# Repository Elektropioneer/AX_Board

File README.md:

# AX_Board
Arduino Nano with support for AX-12A servos with additional buck dc/dc converter

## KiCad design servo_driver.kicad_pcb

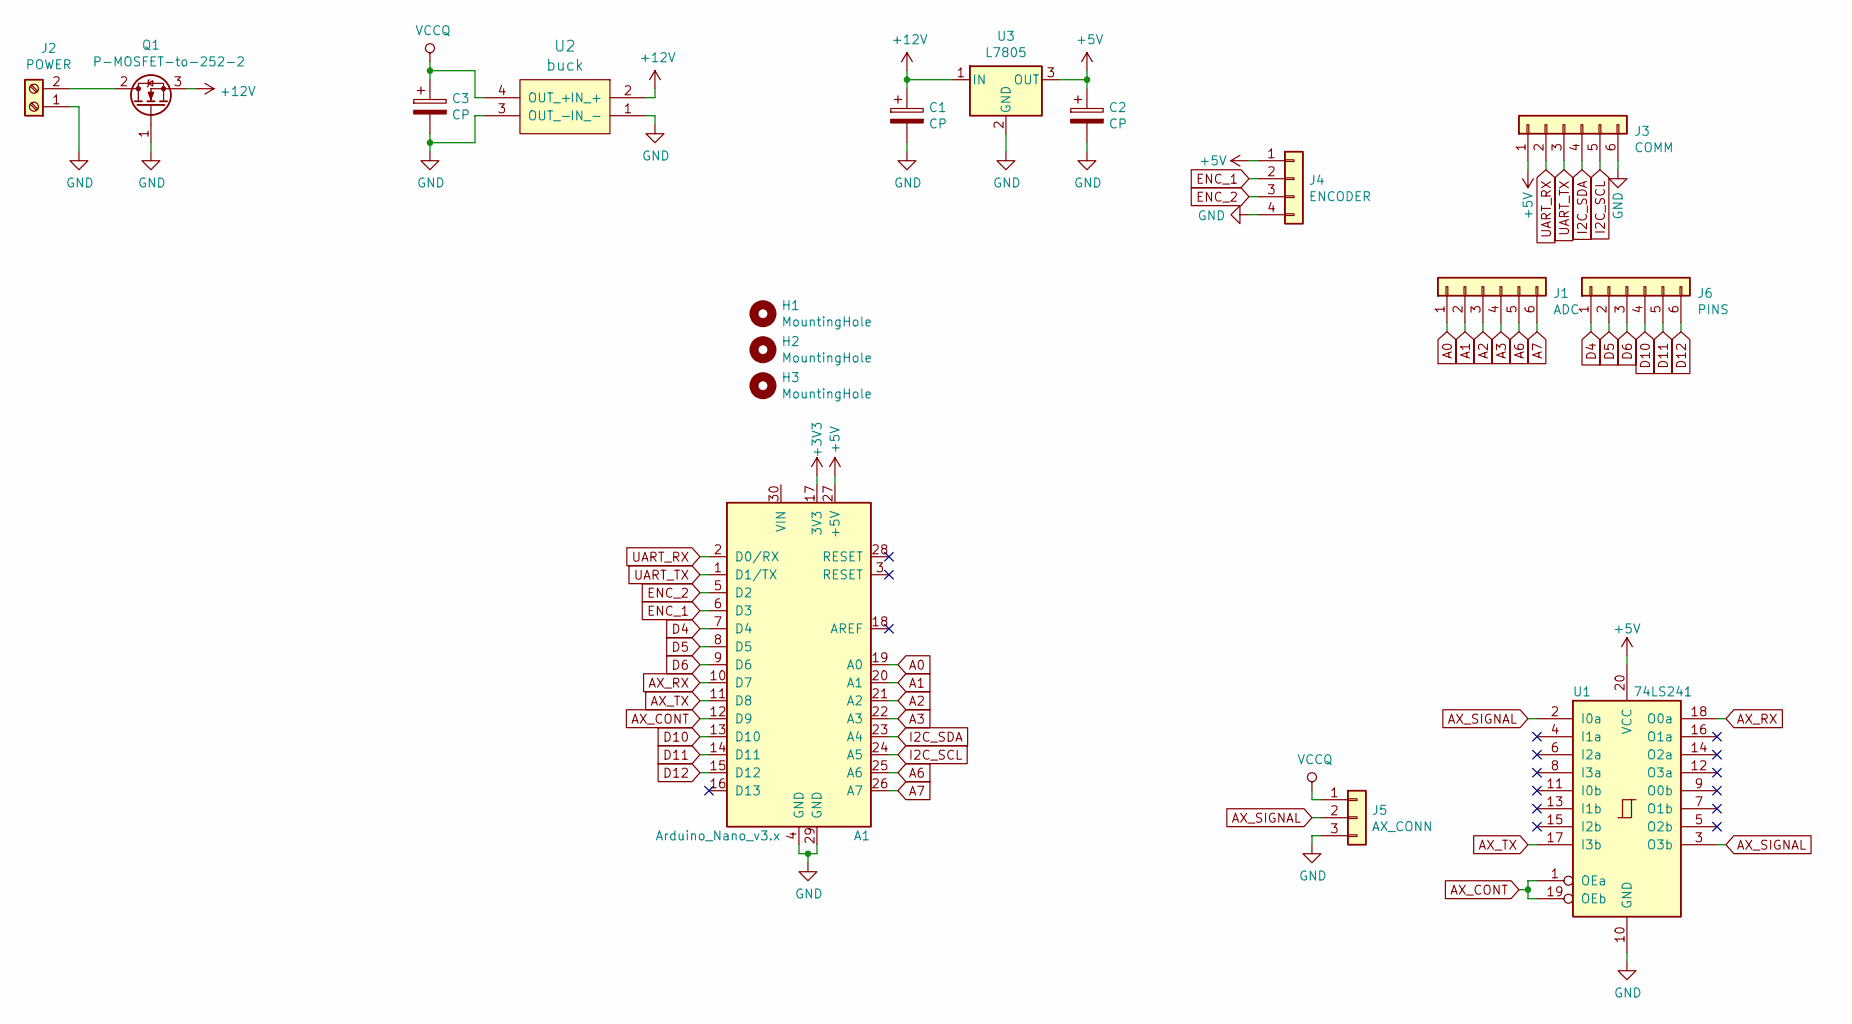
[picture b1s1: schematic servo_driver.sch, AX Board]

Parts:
A1: Arduino_Nano_v3.x; Arduino_Nano
C1, C2, C3: CP; CP_Elec_5x5.8
H1, H2, H3: MountingHole; MountingHole_3.2mm_M3_DIN965_Pad
J1: ADC; PinHeader_1x06_P2.54mm_Vertical
J2: POWER; TerminalBlock_Phoenix_MKDS-1,5-2_1x02_P5.00mm_Horizontal
J3: COMM; PinHeader_1x06_P2.54mm_Vertical
J4: ENCODER; PinHeader_1x04_P2.54mm_Vertical
J5: AX_CONN; TerminalBlock_Phoenix_MKDS-1,5-3_1x03_P5.00mm_Horizontal
J6: PINS; PinHeader_1x06_P2.54mm_Vertical
Q1: P-MOSFET-to-252-2; TO-252-2
U1: 74LS241; DIP-20_W7.62mm
U2: buck
U3: L7805; TO-252-2

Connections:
+3V3: A1.17 (3V3)
+5V: A1.27 (+5V), C2.1, J3.1, J4.1, U1.20 (VCC), U3.3 (OUT)
+12V: C1.1, Q1.3 (S), U2.2 (IN_+), U3.1 (IN)
A0: A1.19 (A0), J1.1
A1: A1.20 (A1), J1.2
A2: A1.21 (A2), J1.3
A3: A1.22 (A3), J1.4
A6: A1.25 (A6), J1.5
A7: A1.26 (A7), J1.6
AX_CONT: A1.12 (D9), U1.1 (OEa), U1.19 (OEb)
AX_RX: A1.10 (D7), U1.18 (O0a)
AX_SIGNAL: J5.2, U1.2 (I0a), U1.3 (O3b)
AX_TX: A1.11 (D8), U1.17 (I3b)
D4: A1.7 (D4), J6.1
D5: A1.8 (D5), J6.2
D6: A1.9 (D6), J6.3
D10: A1.13 (D10), J6.4
D11: A1.14 (D11), J6.5
D12: A1.15 (D12), J6.6
ENC_1: A1.6 (D3), J4.2
ENC_2: A1.5 (D2), J4.3
GND: A1.4 (GND), A1.29 (GND), C1.2, C2.2, C3.2, J2.1, J3.6, J4.4, J5.3, Q1.1 (G), U1.10 (GND), U2.1 (IN_-), U2.3 (OUT_-), U3.2 (GND)
I2C_SCL: A1.24 (A5), J3.5
I2C_SDA: A1.23 (A4), J3.4
unnamed: J2.2, Q1.2 (D)
UART_RX: A1.2 (D0/RX), J3.2
UART_TX: A1.1 (D1/TX), J3.3
VCCQ: C3.1, J5.1, U2.4 (OUT_+)

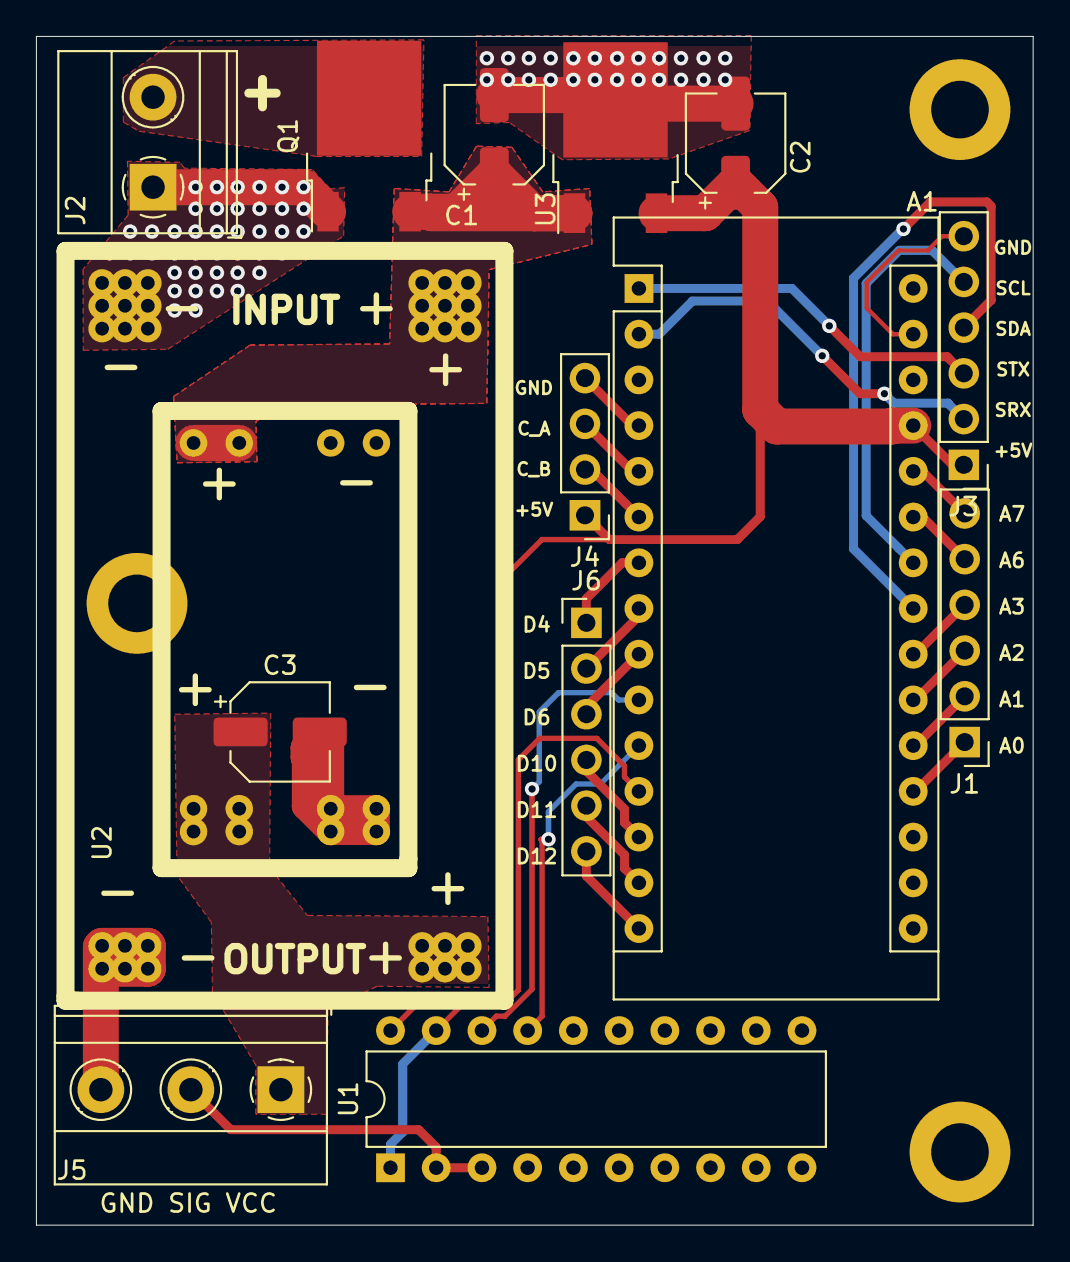
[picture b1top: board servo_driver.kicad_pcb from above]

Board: 2 copper layers, 55.4 x 66.0 mm, 17 parts (0 on the bottom side), 27 nets.

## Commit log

2019-07-16 Main commit
